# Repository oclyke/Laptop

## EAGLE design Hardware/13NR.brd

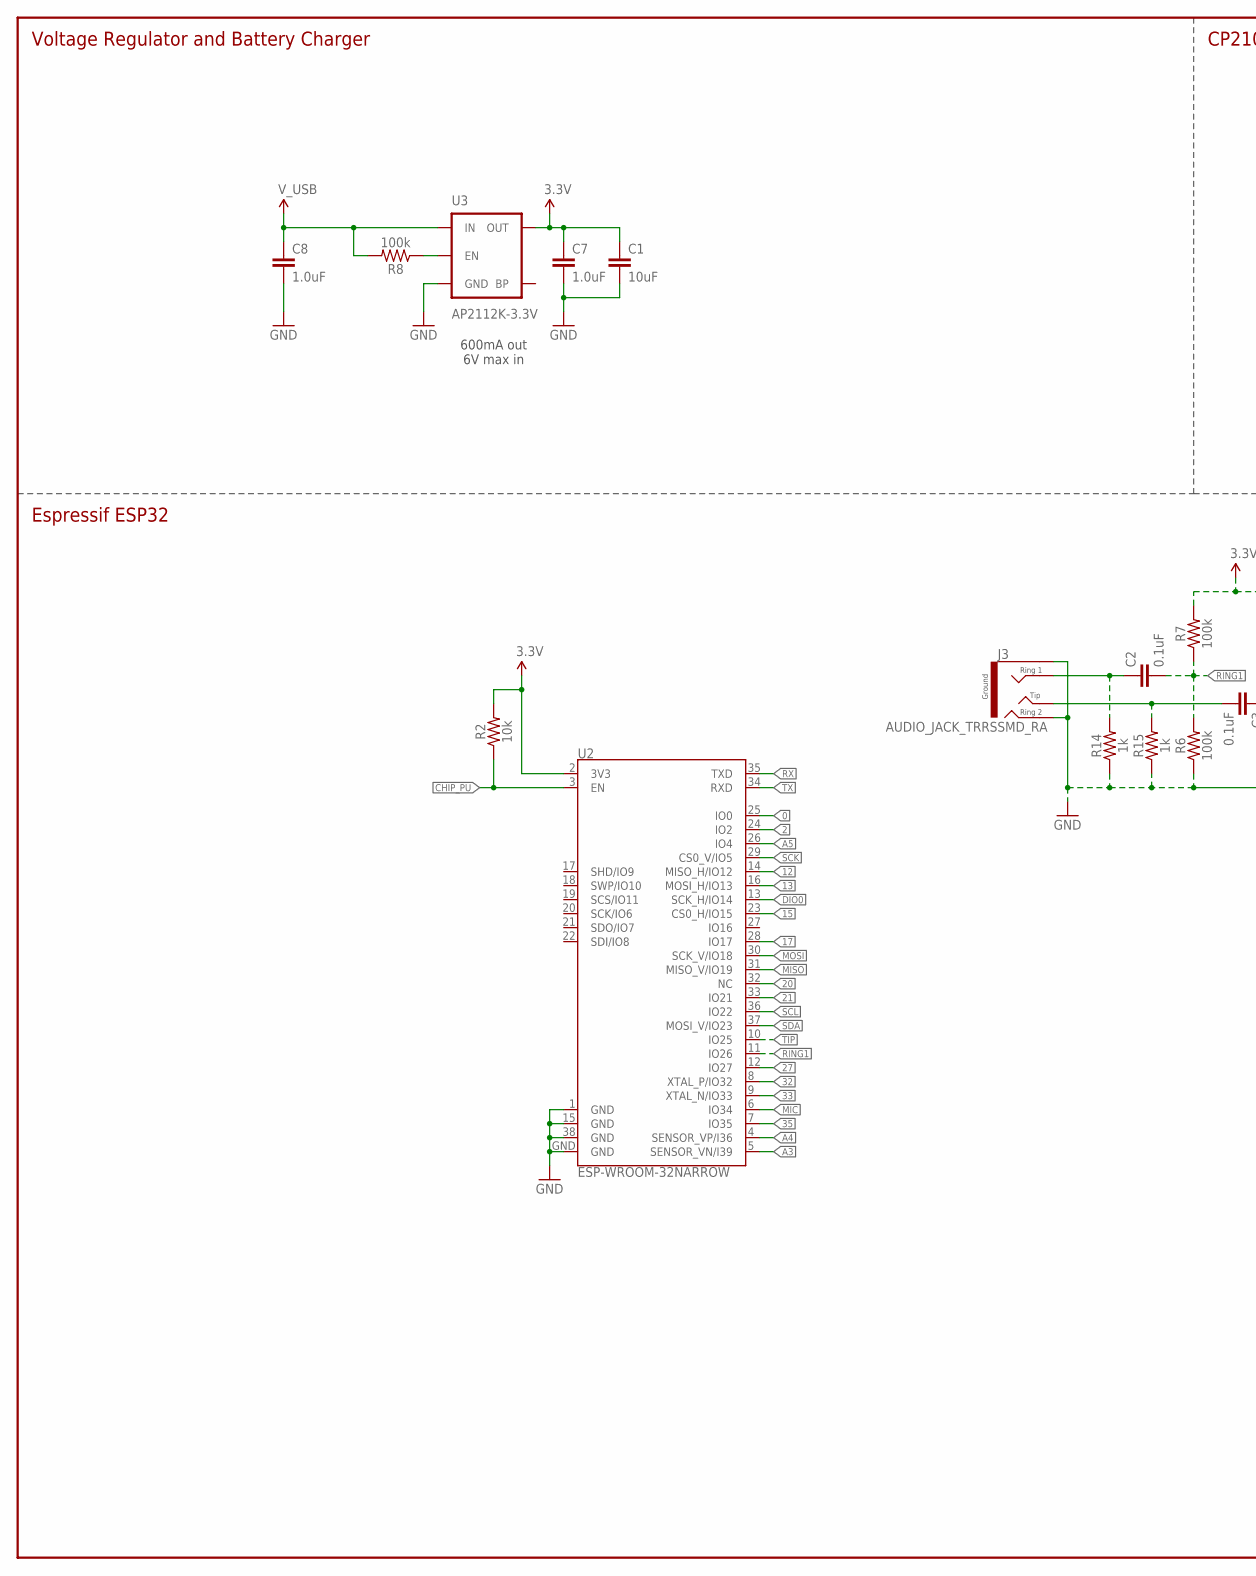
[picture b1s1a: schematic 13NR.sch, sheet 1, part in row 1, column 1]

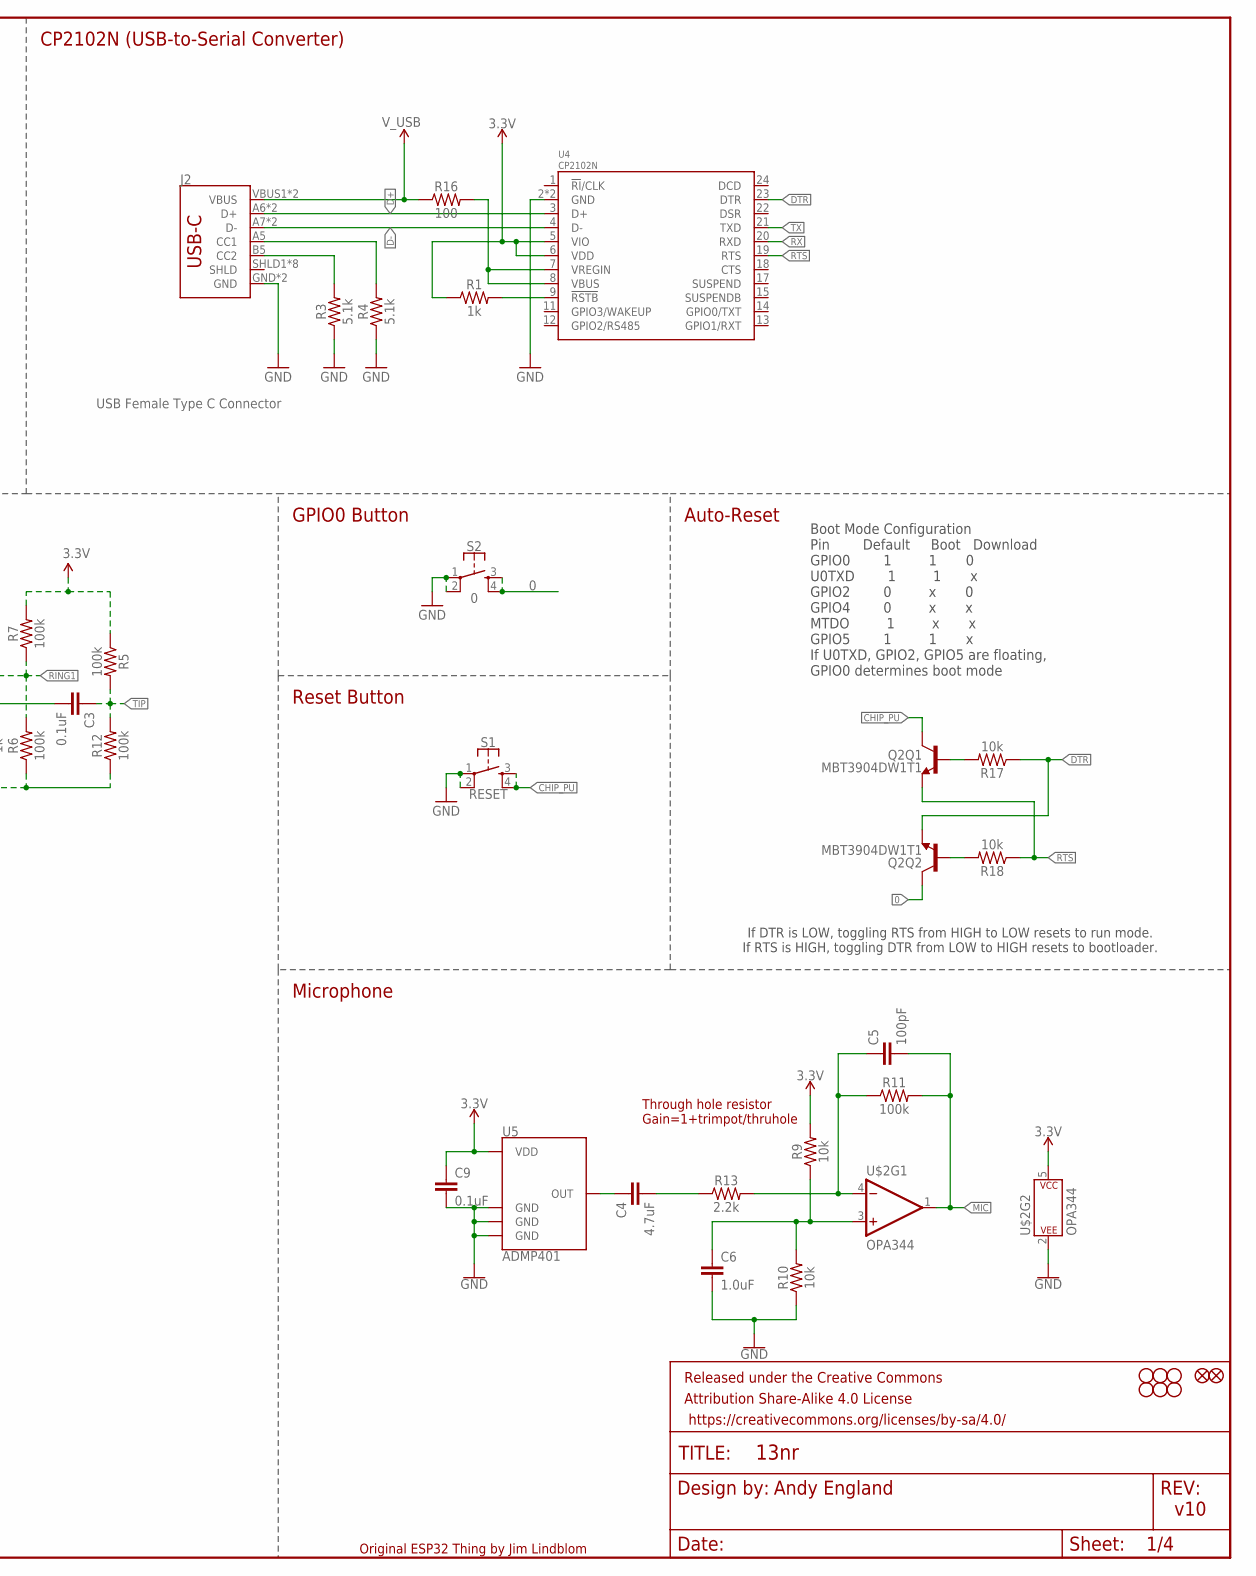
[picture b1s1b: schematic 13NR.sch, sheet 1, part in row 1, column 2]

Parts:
C1: 10uF; 0603
C2, C3, C9: 0.1uF; 0603
C4: 4.7uF; 0603
C5: 100pF; 0603
C6, C7, C8: 1.0uF; 0603
FD1, FD2: FIDUCIALUFIDUCIAL; FIDUCIAL-MICRO
FRAME1: FRAME-LEDGER; CREATIVE_COMMONS
H1, H2, H3, H4, H5, H6: STAND-OFF
J2: USB Female Type C Connector; USB-C-16P
J3: AUDIO_JACK_TRRSSMD_RA; AUDIO_JACK_3.5MM_TRRS_SMD_RA
Q2: MBT3904DW1T1; SC70-6
R1, R14, R15: 1k; 0603
R2, R9, R10, R17, R18: 10k; 0603
R3, R4: 5.1k; 0603
R5, R6, R7, R8, R11, R12: 100k; 0603
R13: 2.2k; 0603
R16: 100; 0603
S1: RESET; TACTILE_SWITCH_SMD_4.6X2.8MM
S2: 0; TACTILE_SWITCH_SMD_4.6X2.8MM
U2: ESP-WROOM-32NARROW; ESP-WROOM-32-NARROW
U3: AP2112K-3.3V; SOT23-5
U4: CP2102N; QFN24
U5: ADMP401
U$2: OPA344; SOT23-5

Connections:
0: Q2.6 (C), S2.3, S2.4, U2.25 (IO0)
2: U2.24 (IO2)
3.3V: C1.1, C7.1, C9.1, R1.1, R2.2, R5.1, R7.2, R9.2, U2.2 (3V3), U3.5 (OUT), U4.5 (VIO), U4.6 (VDD), U5.5 (VDD), U$2.5 (P$V+)
12: U2.14 (MISO_H/IO12)
13: U2.16 (MOSI_H/IO13)
15: U2.23 (CS0_H/IO15)
17: U2.28 (IO17)
20: U2.32 (NC)
21: U2.33 (IO21)
27: U2.12 (IO27)
32: U2.8 (XTAL_P/IO32)
33: U2.9 (XTAL_N/IO33)
35: U2.7 (IO35)
A3: U2.5 (SENSOR_VN/I39)
A4: U2.4 (SENSOR_VP/I36)
A5: U2.26 (IO4)
CHIP_PU: Q2.3 (C), R2.1, S1.3, S1.4, U2.3 (EN)
D+: J2.A6 (D+), J2.B6 (D+), U4.3 (D+)
D-: J2.A7 (D-), J2.B7 (D-), U4.4 (D-)
DIO0: U2.13 (SCK_H/IO14); also elsewhere on the board
DTR: Q2.1 (E), R17.1, U4.23 (DTR)
EN: R8.1, U3.3 (EN)
GND: C1.2, C6.2, C7.2, C8.2, C9.2, J2.GND, J2.GND2 (GND), J3.EARTH, J3.RING2, R3.1, R4.1, R6.1, R10.1, R12.1, R14.1, R15.1, S1.1, S1.2, S2.1, S2.2, U2.1 (GND), U2.15 (GND), U2.38 (GND), U2.GND, U3.2 (GND), U4.2 (GND), U4.PAD (GND), U5.2 (GND), U5.4 (GND), U5.6 (GND), U$2.2 (P$V-); also elsewhere on the board
MIC: C5.2, R11.2, U2.6 (IO34), U$2.1 (OUT)
MISO: U2.31 (MISO_V/IO19)
MOSI: U2.30 (SCK_V/IO18)
unnamed: R1.2, U4.9 (!RSTB)
unnamed: J2.B5 (CC2), R3.2
unnamed: J2.A5 (CC1), R4.2
unnamed: C4.1, U5.1 (OUT)
unnamed: C3.2, J3.TIP, R15.2
unnamed: C2.1, J3.RING1, R14.2
unnamed: C5.1, R11.1, R13.2, U$2.4 (-IN)
unnamed: Q2.5 (B), R17.2
unnamed: C4.2, R13.1
unnamed: Q2.2 (B), R18.2
unnamed: C6.1, R9.1, R10.2, U$2.3 (+IN)
unnamed: R16.2, U4.7 (VREGIN), U4.8 (VBUS)
RING1: C2.2, R6.2, R7.1, U2.11 (IO26)
RTS: Q2.4 (E), R18.1, U4.19 (RTS)
RX: U2.35 (TXD), U4.20 (RXD)
SCK: U2.29 (CS0_V/IO5)
SCL: U2.36 (IO22)
SDA: U2.37 (MOSI_V/IO23)
TIP: C3.1, R5.2, R12.2, U2.10 (IO25)
TX: U2.34 (RXD), U4.21 (TXD)
V_USB: C8.1, J2.VBUS1 (VBUS), J2.VBUS2 (VBUS), R8.2, R16.1, U3.1 (IN); also elsewhere on the board

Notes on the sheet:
Boot Mode Configuration Pin Default Boot Download GPIO0 1 1 0 U0TXD 1 1 x GPIO2 0 x 0 GPIO4 0 x x MTDO 1 x x GPIO5 1 1 x If U0TXD, GPIO2, GPIO5 are floating, GPIO0 determines boot mode
CP2102N (USB-to-Serial Converter)
Voltage Regulator and Battery Charger
600mA out 6V max in
Auto-Reset
Espressif ESP32
Reset Button
Microphone
v10
Original ESP32 Thing by Jim Lindblom
If DTR is LOW, toggling RTS from HIGH to LOW resets to run mode. If RTS is HIGH, toggling DTR from LOW to HIGH resets to bootloader.
Andy England
GPIO0 Button
Through hole resistor Gain=1+trimpot/thruhole

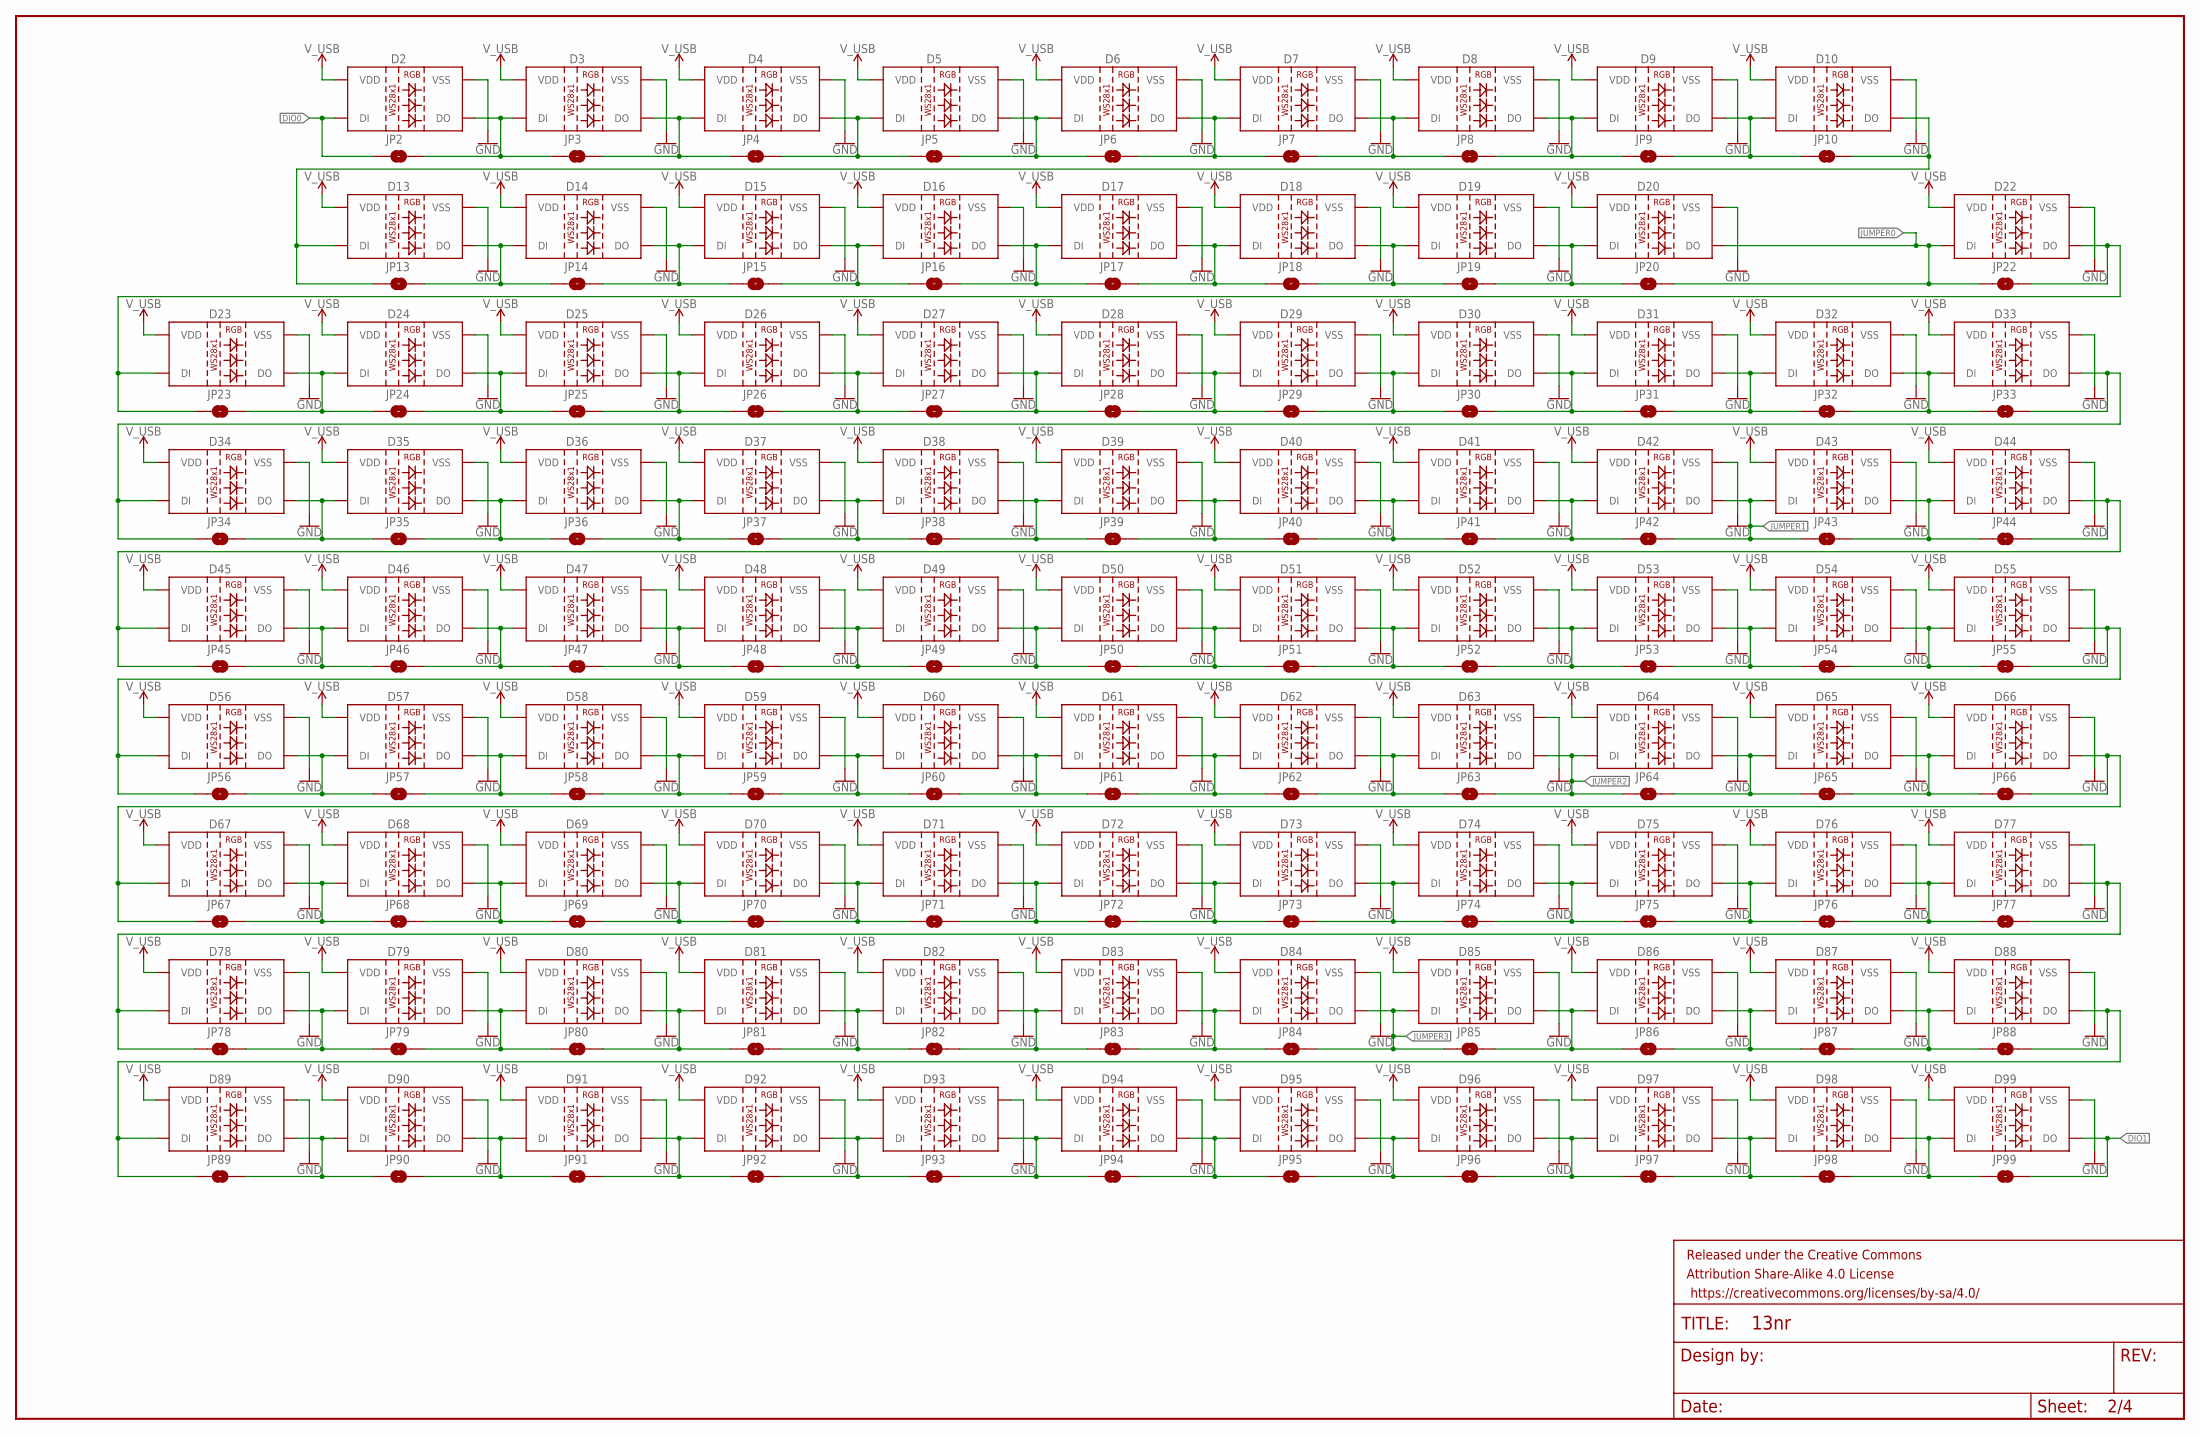
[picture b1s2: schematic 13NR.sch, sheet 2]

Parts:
D2, D3, D4, D5, D6, D7, D8, D9, D10, D13, D14, D15, D16, D17, D18, D19, D20, D22, D23, D24, D25, D26, D27, D28, D29, D30, D31, D32, D33, D34, D35, D36, D37, D38, D39, D40, D41, D42, D43, D44, D45, D46, D47, D48, D49, D50, D51, D52, D53, D54, D55, D56, D57, D58, D59, D60, D61, D62, D63, D64, D65, D66, D67, D68, D69, D70, D71, D72, D73, D74, D75, D76, D77, D78, D79, D80, D81, D82, D83, D84, D85, D86, D87, D88, D89, D90, D91, D92, D93, D94, D95, D96, D97, D98, D99: WS2812B
FRAME2: FRAME-LEDGER; CREATIVE_COMMONS
JP2, JP3, JP4, JP5, JP6, JP7, JP8, JP9, JP10, JP13, JP14, JP15, JP16, JP17, JP18, JP19, JP20, JP22, JP23, JP24, JP25, JP26, JP27, JP28, JP29, JP30, JP31, JP32, JP33, JP34, JP35, JP36, JP37, JP38, JP39, JP40, JP41, JP42, JP43, JP44, JP45, JP46, JP47, JP48, JP49, JP50, JP51, JP52, JP53, JP54, JP55, JP56, JP57, JP58, JP59, JP60, JP61, JP62, JP63, JP64, JP65, JP66, JP67, JP68, JP69, JP70, JP71, JP72, JP73, JP74, JP75, JP76, JP77, JP78, JP79, JP80, JP81, JP82, JP83, JP84, JP85, JP86, JP87, JP88, JP89, JP90, JP91, JP92, JP93, JP94, JP95, JP96, JP97, JP98, JP99: JUMPER-SMT_2_NO_NO-SILK; SMT-JUMPER_2_NO_NO-SILK

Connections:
DIO0: D2.4 (DI), JP2.1; also elsewhere on the board
DIO1: D99.2 (DO), JP99.2; also elsewhere on the board
DIO3: D6.2 (DO), D7.4 (DI), JP6.2, JP7.1
DIO4: D8.2 (DO), D9.4 (DI), JP8.2, JP9.1
DIO6: D13.2 (DO), D14.4 (DI), JP13.2, JP14.1
DIO7: D15.2 (DO), D16.4 (DI), JP15.2, JP16.1
DIO8: D17.2 (DO), D18.4 (DI), JP17.2, JP18.1
DIO9: D19.2 (DO), D20.4 (DI), JP19.2, JP20.1
DIO11: D22.2 (DO), D23.4 (DI), JP22.2, JP23.1
DIO12: D24.2 (DO), D25.4 (DI), JP24.2, JP25.1
DIO13: D26.2 (DO), D27.4 (DI), JP26.2, JP27.1
DIO14: D28.2 (DO), D29.4 (DI), JP28.2, JP29.1
DIO15: D30.2 (DO), D31.4 (DI), JP30.2, JP31.1
DIO16: D32.2 (DO), D33.4 (DI), JP32.2, JP33.1
DIO17: D33.2 (DO), D34.4 (DI), JP33.2, JP34.1
DIO18: D35.2 (DO), D36.4 (DI), JP35.2, JP36.1
DIO19: D37.2 (DO), D38.4 (DI), JP37.2, JP38.1
DIO20: D39.2 (DO), D40.4 (DI), JP39.2, JP40.1
DIO21: D41.2 (DO), D42.4 (DI), JP41.2, JP42.1
DIO22: D43.2 (DO), D44.4 (DI), JP43.2, JP44.1
DIO23: D44.2 (DO), D45.4 (DI), JP44.2, JP45.1
DIO24: D46.2 (DO), D47.4 (DI), JP46.2, JP47.1
DIO25: D48.2 (DO), D49.4 (DI), JP48.2, JP49.1
DIO26: D50.2 (DO), D51.4 (DI), JP50.2, JP51.1
DIO27: D52.2 (DO), D53.4 (DI), JP52.2, JP53.1
DIO28: D54.2 (DO), D55.4 (DI), JP54.2, JP55.1
DIO29: D55.2 (DO), D56.4 (DI), JP55.2, JP56.1
DIO30: D57.2 (DO), D58.4 (DI), JP57.2, JP58.1
DIO31: D59.2 (DO), D60.4 (DI), JP59.2, JP60.1
DIO32: D61.2 (DO), D62.4 (DI), JP61.2, JP62.1
DIO34: D65.2 (DO), D66.4 (DI), JP65.2, JP66.1
DIO35: D66.2 (DO), D67.4 (DI), JP66.2, JP67.1
DIO36: D68.2 (DO), D69.4 (DI), JP68.2, JP69.1
DIO37: D70.2 (DO), D71.4 (DI), JP70.2, JP71.1
DIO38: D72.2 (DO), D73.4 (DI), JP72.2, JP73.1
DIO39: D74.2 (DO), D75.4 (DI), JP74.2, JP75.1
DIO40: D76.2 (DO), D77.4 (DI), JP76.2, JP77.1
DIO41: D77.2 (DO), D78.4 (DI), JP77.2, JP78.1
DIO42: D79.2 (DO), D80.4 (DI), JP79.2, JP80.1
DIO43: D81.2 (DO), D82.4 (DI), JP81.2, JP82.1
DIO44: D83.2 (DO), D84.4 (DI), JP83.2, JP84.1
DIO45: D85.2 (DO), D86.4 (DI), JP85.2, JP86.1
DIO46: D87.2 (DO), D88.4 (DI), JP87.2, JP88.1
DIO47: D88.2 (DO), D89.4 (DI), JP88.2, JP89.1
DIO48: D90.2 (DO), D91.4 (DI), JP90.2, JP91.1
DIO49: D92.2 (DO), D93.4 (DI), JP92.2, JP93.1
DIO50: D94.2 (DO), D95.4 (DI), JP94.2, JP95.1
DIO51: D96.2 (DO), D97.4 (DI), JP96.2, JP97.1
DIO52: D98.2 (DO), D99.4 (DI), JP98.2, JP99.1
GND: D2.3 (VSS), D3.3 (VSS), D4.3 (VSS), D5.3 (VSS), D6.3 (VSS), D7.3 (VSS), D8.3 (VSS), D9.3 (VSS), D10.3 (VSS), D13.3 (VSS), D14.3 (VSS), D15.3 (VSS), D16.3 (VSS), D17.3 (VSS), D18.3 (VSS), D19.3 (VSS), D20.3 (VSS), D22.3 (VSS), D23.3 (VSS), D24.3 (VSS), D25.3 (VSS), D26.3 (VSS), D27.3 (VSS), D28.3 (VSS), D29.3 (VSS), D30.3 (VSS), D31.3 (VSS), D32.3 (VSS), D33.3 (VSS), D34.3 (VSS), D35.3 (VSS), D36.3 (VSS), D37.3 (VSS), D38.3 (VSS), D39.3 (VSS), D40.3 (VSS), D41.3 (VSS), D42.3 (VSS), D43.3 (VSS), D44.3 (VSS), D45.3 (VSS), D46.3 (VSS), D47.3 (VSS), D48.3 (VSS), D49.3 (VSS), D50.3 (VSS), D51.3 (VSS), D52.3 (VSS), D53.3 (VSS), D54.3 (VSS), D55.3 (VSS), D56.3 (VSS), D57.3 (VSS), D58.3 (VSS), D59.3 (VSS), D60.3 (VSS), D61.3 (VSS), D62.3 (VSS), D63.3 (VSS), D64.3 (VSS), D65.3 (VSS), D66.3 (VSS), D67.3 (VSS), D68.3 (VSS), D69.3 (VSS), D70.3 (VSS), D71.3 (VSS), D72.3 (VSS), D73.3 (VSS), D74.3 (VSS), D75.3 (VSS), D76.3 (VSS), D77.3 (VSS), D78.3 (VSS), D79.3 (VSS), D80.3 (VSS), D81.3 (VSS), D82.3 (VSS), D83.3 (VSS), D84.3 (VSS), D85.3 (VSS), D86.3 (VSS), D87.3 (VSS), D88.3 (VSS), D89.3 (VSS), D90.3 (VSS), D91.3 (VSS), D92.3 (VSS), D93.3 (VSS), D94.3 (VSS), D95.3 (VSS), D96.3 (VSS), D97.3 (VSS), D98.3 (VSS), D99.3 (VSS); also elsewhere on the board
JUMPER0: D20.2 (DO), D22.4 (DI), JP20.2, JP22.1; also elsewhere on the board
JUMPER1: D42.2 (DO), D43.4 (DI), JP42.2, JP43.1; also elsewhere on the board
JUMPER2: D63.2 (DO), D64.4 (DI), JP63.2, JP64.1; also elsewhere on the board
JUMPER3: D84.2 (DO), D85.4 (DI), JP84.2, JP85.1; also elsewhere on the board
unnamed: D3.2 (DO), D4.4 (DI), JP3.2, JP4.1
unnamed: D5.2 (DO), D6.4 (DI), JP5.2, JP6.1
unnamed: D9.2 (DO), D10.4 (DI), JP9.2, JP10.1
unnamed: D7.2 (DO), D8.4 (DI), JP7.2, JP8.1
unnamed: D16.2 (DO), D17.4 (DI), JP16.2, JP17.1
unnamed: D23.2 (DO), D24.4 (DI), JP23.2, JP24.1
unnamed: D14.2 (DO), D15.4 (DI), JP14.2, JP15.1
unnamed: D18.2 (DO), D19.4 (DI), JP18.2, JP19.1
unnamed: D27.2 (DO), D28.4 (DI), JP27.2, JP28.1
unnamed: D25.2 (DO), D26.4 (DI), JP25.2, JP26.1
unnamed: D31.2 (DO), D32.4 (DI), JP31.2, JP32.1
unnamed: D29.2 (DO), D30.4 (DI), JP29.2, JP30.1
unnamed: D34.2 (DO), D35.4 (DI), JP34.2, JP35.1
unnamed: D38.2 (DO), D39.4 (DI), JP38.2, JP39.1
unnamed: D36.2 (DO), D37.4 (DI), JP36.2, JP37.1
unnamed: D40.2 (DO), D41.4 (DI), JP40.2, JP41.1
unnamed: D45.2 (DO), D46.4 (DI), JP45.2, JP46.1
unnamed: D49.2 (DO), D50.4 (DI), JP49.2, JP50.1
unnamed: D47.2 (DO), D48.4 (DI), JP47.2, JP48.1
unnamed: D53.2 (DO), D54.4 (DI), JP53.2, JP54.1
unnamed: D51.2 (DO), D52.4 (DI), JP51.2, JP52.1
unnamed: D56.2 (DO), D57.4 (DI), JP56.2, JP57.1
unnamed: D60.2 (DO), D61.4 (DI), JP60.2, JP61.1
unnamed: D58.2 (DO), D59.4 (DI), JP58.2, JP59.1
unnamed: D64.2 (DO), D65.4 (DI), JP64.2, JP65.1
unnamed: D62.2 (DO), D63.4 (DI), JP62.2, JP63.1
unnamed: D67.2 (DO), D68.4 (DI), JP67.2, JP68.1
unnamed: D71.2 (DO), D72.4 (DI), JP71.2, JP72.1
unnamed: D69.2 (DO), D70.4 (DI), JP69.2, JP70.1
unnamed: D75.2 (DO), D76.4 (DI), JP75.2, JP76.1
unnamed: D73.2 (DO), D74.4 (DI), JP73.2, JP74.1
unnamed: D78.2 (DO), D79.4 (DI), JP78.2, JP79.1
unnamed: D82.2 (DO), D83.4 (DI), JP82.2, JP83.1
unnamed: D80.2 (DO), D81.4 (DI), JP80.2, JP81.1
unnamed: D86.2 (DO), D87.4 (DI), JP86.2, JP87.1
unnamed: D89.2 (DO), D90.4 (DI), JP89.2, JP90.1
unnamed: D93.2 (DO), D94.4 (DI), JP93.2, JP94.1
unnamed: D91.2 (DO), D92.4 (DI), JP91.2, JP92.1
unnamed: D97.2 (DO), D98.4 (DI), JP97.2, JP98.1
unnamed: D95.2 (DO), D96.4 (DI), JP95.2, JP96.1
unnamed: D2.2 (DO), D3.4 (DI), JP2.2, JP3.1
unnamed: D4.2 (DO), D5.4 (DI), JP4.2, JP5.1
unnamed: D10.2 (DO), D13.4 (DI), JP10.2, JP13.1
V_USB: D2.1 (VDD), D3.1 (VDD), D4.1 (VDD), D5.1 (VDD), D6.1 (VDD), D7.1 (VDD), D8.1 (VDD), D9.1 (VDD), D10.1 (VDD), D13.1 (VDD), D14.1 (VDD), D15.1 (VDD), D16.1 (VDD), D17.1 (VDD), D18.1 (VDD), D19.1 (VDD), D20.1 (VDD), D22.1 (VDD), D23.1 (VDD), D24.1 (VDD), D25.1 (VDD), D26.1 (VDD), D27.1 (VDD), D28.1 (VDD), D29.1 (VDD), D30.1 (VDD), D31.1 (VDD), D32.1 (VDD), D33.1 (VDD), D34.1 (VDD), D35.1 (VDD), D36.1 (VDD), D37.1 (VDD), D38.1 (VDD), D39.1 (VDD), D40.1 (VDD), D41.1 (VDD), D42.1 (VDD), D43.1 (VDD), D44.1 (VDD), D45.1 (VDD), D46.1 (VDD), D47.1 (VDD), D48.1 (VDD), D49.1 (VDD), D50.1 (VDD), D51.1 (VDD), D52.1 (VDD), D53.1 (VDD), D54.1 (VDD), D55.1 (VDD), D56.1 (VDD), D57.1 (VDD), D58.1 (VDD), D59.1 (VDD), D60.1 (VDD), D61.1 (VDD), D62.1 (VDD), D63.1 (VDD), D64.1 (VDD), D65.1 (VDD), D66.1 (VDD), D67.1 (VDD), D68.1 (VDD), D69.1 (VDD), D70.1 (VDD), D71.1 (VDD), D72.1 (VDD), D73.1 (VDD), D74.1 (VDD), D75.1 (VDD), D76.1 (VDD), D77.1 (VDD), D78.1 (VDD), D79.1 (VDD), D80.1 (VDD), D81.1 (VDD), D82.1 (VDD), D83.1 (VDD), D84.1 (VDD), D85.1 (VDD), D86.1 (VDD), D87.1 (VDD), D88.1 (VDD), D89.1 (VDD), D90.1 (VDD), D91.1 (VDD), D92.1 (VDD), D93.1 (VDD), D94.1 (VDD), D95.1 (VDD), D96.1 (VDD), D97.1 (VDD), D98.1 (VDD), D99.1 (VDD); also elsewhere on the board

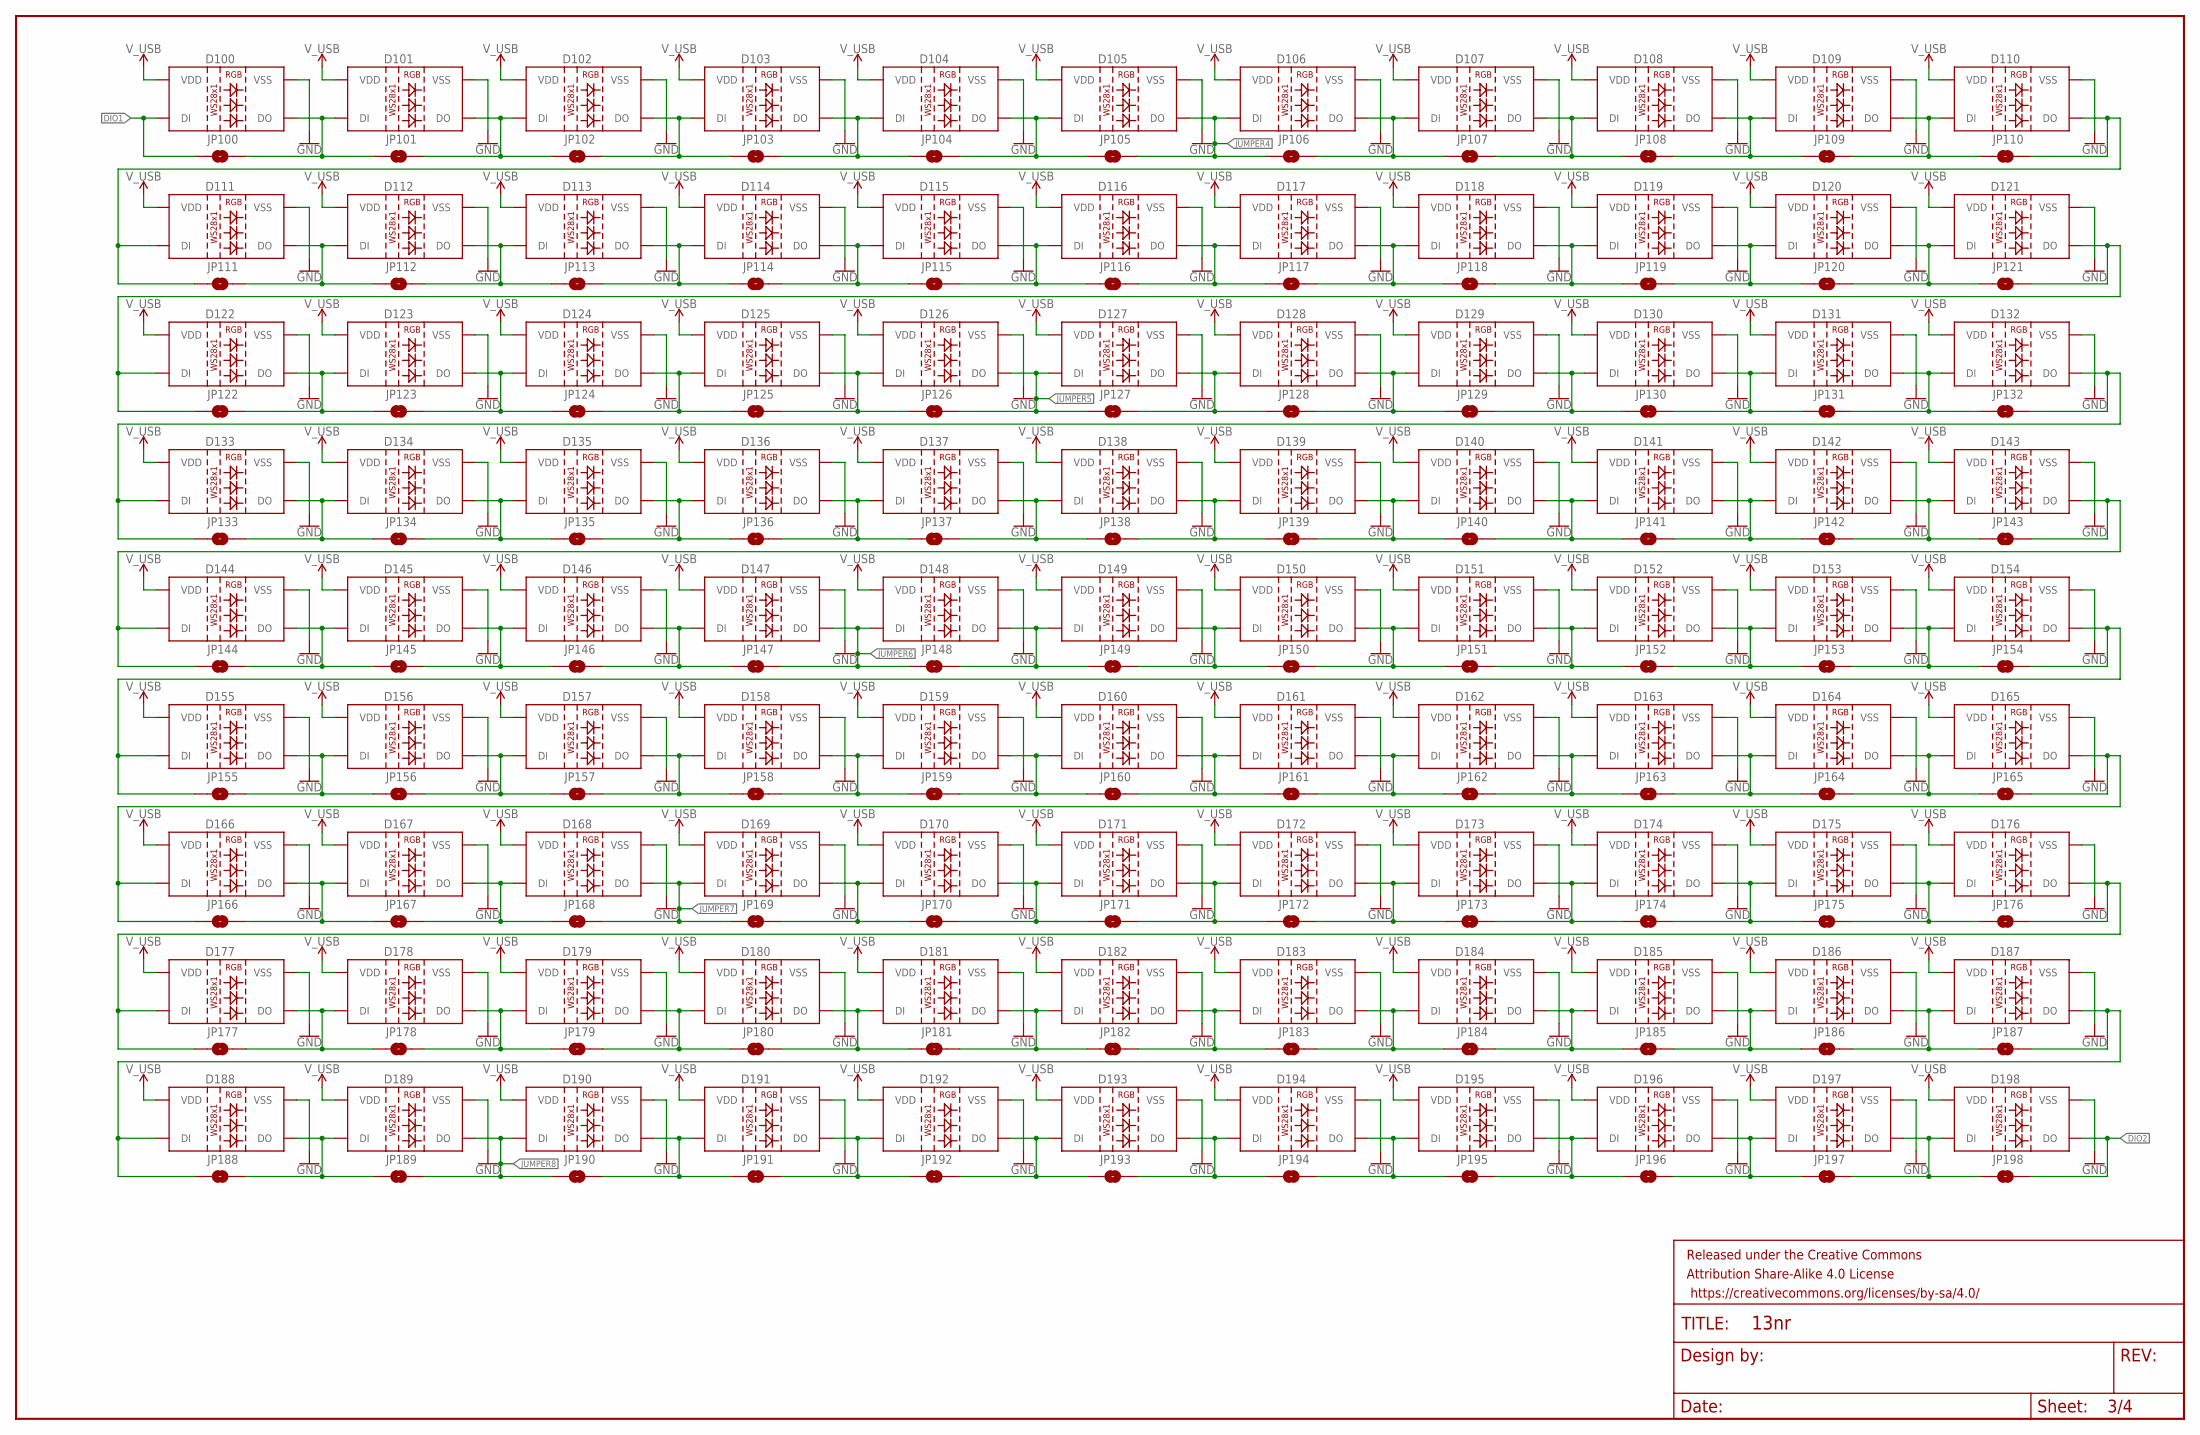
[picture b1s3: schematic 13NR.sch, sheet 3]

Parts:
D100, D101, D102, D103, D104, D105, D106, D107, D108, D109, D110, D111, D112, D113, D114, D115, D116, D117, D118, D119, D120, D121, D122, D123, D124, D125, D126, D127, D128, D129, D130, D131, D132, D133, D134, D135, D136, D137, D138, D139, D140, D141, D142, D143, D144, D145, D146, D147, D148, D149, D150, D151, D152, D153, D154, D155, D156, D157, D158, D159, D160, D161, D162, D163, D164, D165, D166, D167, D168, D169, D170, D171, D172, D173, D174, D175, D176, D177, D178, D179, D180, D181, D182, D183, D184, D185, D186, D187, D188, D189, D190, D191, D192, D193, D194, D195, D196, D197, D198: WS2812B
FRAME3: FRAME-LEDGER; CREATIVE_COMMONS
JP100, JP101, JP102, JP103, JP104, JP105, JP106, JP107, JP108, JP109, JP110, JP111, JP112, JP113, JP114, JP115, JP116, JP117, JP118, JP119, JP120, JP121, JP122, JP123, JP124, JP125, JP126, JP127, JP128, JP129, JP130, JP131, JP132, JP133, JP134, JP135, JP136, JP137, JP138, JP139, JP140, JP141, JP142, JP143, JP144, JP145, JP146, JP147, JP148, JP149, JP150, JP151, JP152, JP153, JP154, JP155, JP156, JP157, JP158, JP159, JP160, JP161, JP162, JP163, JP164, JP165, JP166, JP167, JP168, JP169, JP170, JP171, JP172, JP173, JP174, JP175, JP176, JP177, JP178, JP179, JP180, JP181, JP182, JP183, JP184, JP185, JP186, JP187, JP188, JP189, JP190, JP191, JP192, JP193, JP194, JP195, JP196, JP197, JP198: JUMPER-SMT_2_NO_NO-SILK; SMT-JUMPER_2_NO_NO-SILK

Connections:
DIO1: D100.4 (DI), JP100.1; also elsewhere on the board
DIO2: D198.2 (DO), JP198.2; also elsewhere on the board
DIO53: D103.2 (DO), D104.4 (DI), JP103.2, JP104.1
DIO55: D107.2 (DO), D108.4 (DI), JP107.2, JP108.1
DIO56: D109.2 (DO), D110.4 (DI), JP109.2, JP110.1
DIO57: D112.2 (DO), D113.4 (DI), JP112.2, JP113.1
DIO58: D114.2 (DO), D115.4 (DI), JP114.2, JP115.1
DIO59: D116.2 (DO), D117.4 (DI), JP116.2, JP117.1
DIO60: D118.2 (DO), D119.4 (DI), JP118.2, JP119.1
DIO61: D120.2 (DO), D121.4 (DI), JP120.2, JP121.1
DIO62: D121.2 (DO), D122.4 (DI), JP121.2, JP122.1
DIO63: D123.2 (DO), D124.4 (DI), JP123.2, JP124.1
DIO64: D125.2 (DO), D126.4 (DI), JP125.2, JP126.1
DIO65: D127.2 (DO), D128.4 (DI), JP127.2, JP128.1
DIO66: D129.2 (DO), D130.4 (DI), JP129.2, JP130.1
DIO67: D131.2 (DO), D132.4 (DI), JP131.2, JP132.1
DIO68: D132.2 (DO), D133.4 (DI), JP132.2, JP133.1
DIO69: D134.2 (DO), D135.4 (DI), JP134.2, JP135.1
DIO70: D136.2 (DO), D137.4 (DI), JP136.2, JP137.1
DIO71: D138.2 (DO), D139.4 (DI), JP138.2, JP139.1
DIO72: D140.2 (DO), D141.4 (DI), JP140.2, JP141.1
DIO73: D142.2 (DO), D143.4 (DI), JP142.2, JP143.1
DIO74: D143.2 (DO), D144.4 (DI), JP143.2, JP144.1
DIO75: D145.2 (DO), D146.4 (DI), JP145.2, JP146.1
DIO77: D149.2 (DO), D150.4 (DI), JP149.2, JP150.1
DIO78: D151.2 (DO), D152.4 (DI), JP151.2, JP152.1
DIO79: D153.2 (DO), D154.4 (DI), JP153.2, JP154.1
DIO80: D154.2 (DO), D155.4 (DI), JP154.2, JP155.1
DIO81: D156.2 (DO), D157.4 (DI), JP156.2, JP157.1
DIO82: D158.2 (DO), D159.4 (DI), JP158.2, JP159.1
DIO83: D160.2 (DO), D161.4 (DI), JP160.2, JP161.1
DIO84: D162.2 (DO), D163.4 (DI), JP162.2, JP163.1
DIO85: D164.2 (DO), D165.4 (DI), JP164.2, JP165.1
DIO86: D165.2 (DO), D166.4 (DI), JP165.2, JP166.1
DIO87: D167.2 (DO), D168.4 (DI), JP167.2, JP168.1
DIO88: D169.2 (DO), D170.4 (DI), JP169.2, JP170.1
DIO89: D171.2 (DO), D172.4 (DI), JP171.2, JP172.1
DIO90: D173.2 (DO), D174.4 (DI), JP173.2, JP174.1
DIO91: D175.2 (DO), D176.4 (DI), JP175.2, JP176.1
DIO92: D176.2 (DO), D177.4 (DI), JP176.2, JP177.1
DIO93: D178.2 (DO), D179.4 (DI), JP178.2, JP179.1
DIO94: D180.2 (DO), D181.4 (DI), JP180.2, JP181.1
DIO95: D182.2 (DO), D183.4 (DI), JP182.2, JP183.1
DIO96: D184.2 (DO), D185.4 (DI), JP184.2, JP185.1
DIO97: D186.2 (DO), D187.4 (DI), JP186.2, JP187.1
DIO98: D187.2 (DO), D188.4 (DI), JP187.2, JP188.1
DIO100: D191.2 (DO), D192.4 (DI), JP191.2, JP192.1
DIO101: D193.2 (DO), D194.4 (DI), JP193.2, JP194.1
DIO102: D195.2 (DO), D196.4 (DI), JP195.2, JP196.1
DIO103: D197.2 (DO), D198.4 (DI), JP197.2, JP198.1
GND: D100.3 (VSS), D101.3 (VSS), D102.3 (VSS), D103.3 (VSS), D104.3 (VSS), D105.3 (VSS), D106.3 (VSS), D107.3 (VSS), D108.3 (VSS), D109.3 (VSS), D110.3 (VSS), D111.3 (VSS), D112.3 (VSS), D113.3 (VSS), D114.3 (VSS), D115.3 (VSS), D116.3 (VSS), D117.3 (VSS), D118.3 (VSS), D119.3 (VSS), D120.3 (VSS), D121.3 (VSS), D122.3 (VSS), D123.3 (VSS), D124.3 (VSS), D125.3 (VSS), D126.3 (VSS), D127.3 (VSS), D128.3 (VSS), D129.3 (VSS), D130.3 (VSS), D131.3 (VSS), D132.3 (VSS), D133.3 (VSS), D134.3 (VSS), D135.3 (VSS), D136.3 (VSS), D137.3 (VSS), D138.3 (VSS), D139.3 (VSS), D140.3 (VSS), D141.3 (VSS), D142.3 (VSS), D143.3 (VSS), D144.3 (VSS), D145.3 (VSS), D146.3 (VSS), D147.3 (VSS), D148.3 (VSS), D149.3 (VSS), D150.3 (VSS), D151.3 (VSS), D152.3 (VSS), D153.3 (VSS), D154.3 (VSS), D155.3 (VSS), D156.3 (VSS), D157.3 (VSS), D158.3 (VSS), D159.3 (VSS), D160.3 (VSS), D161.3 (VSS), D162.3 (VSS), D163.3 (VSS), D164.3 (VSS), D165.3 (VSS), D166.3 (VSS), D167.3 (VSS), D168.3 (VSS), D169.3 (VSS), D170.3 (VSS), D171.3 (VSS), D172.3 (VSS), D173.3 (VSS), D174.3 (VSS), D175.3 (VSS), D176.3 (VSS), D177.3 (VSS), D178.3 (VSS), D179.3 (VSS), D180.3 (VSS), D181.3 (VSS), D182.3 (VSS), D183.3 (VSS), D184.3 (VSS), D185.3 (VSS), D186.3 (VSS), D187.3 (VSS), D188.3 (VSS), D189.3 (VSS), D190.3 (VSS), D191.3 (VSS), D192.3 (VSS), D193.3 (VSS), D194.3 (VSS), D195.3 (VSS), D196.3 (VSS), D197.3 (VSS), D198.3 (VSS); also elsewhere on the board
JUMPER4: D105.2 (DO), D106.4 (DI), JP105.2, JP106.1; also elsewhere on the board
JUMPER5: D126.2 (DO), D127.4 (DI), JP126.2, JP127.1; also elsewhere on the board
JUMPER6: D147.2 (DO), D148.4 (DI), JP147.2, JP148.1; also elsewhere on the board
JUMPER7: D168.2 (DO), D169.4 (DI), JP168.2, JP169.1; also elsewhere on the board
JUMPER8: D189.2 (DO), D190.4 (DI), JP189.2, JP190.1; also elsewhere on the board
unnamed: D100.2 (DO), D101.4 (DI), JP100.2, JP101.1
unnamed: D104.2 (DO), D105.4 (DI), JP104.2, JP105.1
unnamed: D102.2 (DO), D103.4 (DI), JP102.2, JP103.1
unnamed: D108.2 (DO), D109.4 (DI), JP108.2, JP109.1
unnamed: D106.2 (DO), D107.4 (DI), JP106.2, JP107.1
unnamed: D111.2 (DO), D112.4 (DI), JP111.2, JP112.1
unnamed: D115.2 (DO), D116.4 (DI), JP115.2, JP116.1
unnamed: D113.2 (DO), D114.4 (DI), JP113.2, JP114.1
unnamed: D119.2 (DO), D120.4 (DI), JP119.2, JP120.1
unnamed: D117.2 (DO), D118.4 (DI), JP117.2, JP118.1
unnamed: D122.2 (DO), D123.4 (DI), JP122.2, JP123.1
unnamed: D124.2 (DO), D125.4 (DI), JP124.2, JP125.1
unnamed: D130.2 (DO), D131.4 (DI), JP130.2, JP131.1
unnamed: D128.2 (DO), D129.4 (DI), JP128.2, JP129.1
unnamed: D133.2 (DO), D134.4 (DI), JP133.2, JP134.1
unnamed: D137.2 (DO), D138.4 (DI), JP137.2, JP138.1
unnamed: D135.2 (DO), D136.4 (DI), JP135.2, JP136.1
unnamed: D141.2 (DO), D142.4 (DI), JP141.2, JP142.1
unnamed: D139.2 (DO), D140.4 (DI), JP139.2, JP140.1
unnamed: D144.2 (DO), D145.4 (DI), JP144.2, JP145.1
unnamed: D148.2 (DO), D149.4 (DI), JP148.2, JP149.1
unnamed: D146.2 (DO), D147.4 (DI), JP146.2, JP147.1
unnamed: D152.2 (DO), D153.4 (DI), JP152.2, JP153.1
unnamed: D150.2 (DO), D151.4 (DI), JP150.2, JP151.1
unnamed: D155.2 (DO), D156.4 (DI), JP155.2, JP156.1
unnamed: D159.2 (DO), D160.4 (DI), JP159.2, JP160.1
unnamed: D157.2 (DO), D158.4 (DI), JP157.2, JP158.1
unnamed: D163.2 (DO), D164.4 (DI), JP163.2, JP164.1
unnamed: D161.2 (DO), D162.4 (DI), JP161.2, JP162.1
unnamed: D166.2 (DO), D167.4 (DI), JP166.2, JP167.1
unnamed: D170.2 (DO), D171.4 (DI), JP170.2, JP171.1
unnamed: D174.2 (DO), D175.4 (DI), JP174.2, JP175.1
unnamed: D172.2 (DO), D173.4 (DI), JP172.2, JP173.1
unnamed: D177.2 (DO), D178.4 (DI), JP177.2, JP178.1
unnamed: D181.2 (DO), D182.4 (DI), JP181.2, JP182.1
unnamed: D179.2 (DO), D180.4 (DI), JP179.2, JP180.1
unnamed: D185.2 (DO), D186.4 (DI), JP185.2, JP186.1
unnamed: D183.2 (DO), D184.4 (DI), JP183.2, JP184.1
unnamed: D188.2 (DO), D189.4 (DI), JP188.2, JP189.1
unnamed: D192.2 (DO), D193.4 (DI), JP192.2, JP193.1
unnamed: D190.2 (DO), D191.4 (DI), JP190.2, JP191.1
unnamed: D196.2 (DO), D197.4 (DI), JP196.2, JP197.1
unnamed: D194.2 (DO), D195.4 (DI), JP194.2, JP195.1
unnamed: D101.2 (DO), D102.4 (DI), JP101.2, JP102.1
unnamed: D110.2 (DO), D111.4 (DI), JP110.2, JP111.1
V_USB: D100.1 (VDD), D101.1 (VDD), D102.1 (VDD), D103.1 (VDD), D104.1 (VDD), D105.1 (VDD), D106.1 (VDD), D107.1 (VDD), D108.1 (VDD), D109.1 (VDD), D110.1 (VDD), D111.1 (VDD), D112.1 (VDD), D113.1 (VDD), D114.1 (VDD), D115.1 (VDD), D116.1 (VDD), D117.1 (VDD), D118.1 (VDD), D119.1 (VDD), D120.1 (VDD), D121.1 (VDD), D122.1 (VDD), D123.1 (VDD), D124.1 (VDD), D125.1 (VDD), D126.1 (VDD), D127.1 (VDD), D128.1 (VDD), D129.1 (VDD), D130.1 (VDD), D131.1 (VDD), D132.1 (VDD), D133.1 (VDD), D134.1 (VDD), D135.1 (VDD), D136.1 (VDD), D137.1 (VDD), D138.1 (VDD), D139.1 (VDD), D140.1 (VDD), D141.1 (VDD), D142.1 (VDD), D143.1 (VDD), D144.1 (VDD), D145.1 (VDD), D146.1 (VDD), D147.1 (VDD), D148.1 (VDD), D149.1 (VDD), D150.1 (VDD), D151.1 (VDD), D152.1 (VDD), D153.1 (VDD), D154.1 (VDD), D155.1 (VDD), D156.1 (VDD), D157.1 (VDD), D158.1 (VDD), D159.1 (VDD), D160.1 (VDD), D161.1 (VDD), D162.1 (VDD), D163.1 (VDD), D164.1 (VDD), D165.1 (VDD), D166.1 (VDD), D167.1 (VDD), D168.1 (VDD), D169.1 (VDD), D170.1 (VDD), D171.1 (VDD), D172.1 (VDD), D173.1 (VDD), D174.1 (VDD), D175.1 (VDD), D176.1 (VDD), D177.1 (VDD), D178.1 (VDD), D179.1 (VDD), D180.1 (VDD), D181.1 (VDD), D182.1 (VDD), D183.1 (VDD), D184.1 (VDD), D185.1 (VDD), D186.1 (VDD), D187.1 (VDD), D188.1 (VDD), D189.1 (VDD), D190.1 (VDD), D191.1 (VDD), D192.1 (VDD), D193.1 (VDD), D194.1 (VDD), D195.1 (VDD), D196.1 (VDD), D197.1 (VDD), D198.1 (VDD); also elsewhere on the board

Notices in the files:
parts and their libraries:
SparkFun-Capacitors: Licensing: Creative Commons ShareAlike 4.0 International - https://creativecommons.org/licenses/by-sa/4.0
SparkFun-Aesthetics: Released under the Creative Commons Attribution Share-Alike 4.0 License
SparkFun-Aesthetics: https://creativecommons.org/licenses/by-sa/4.0
